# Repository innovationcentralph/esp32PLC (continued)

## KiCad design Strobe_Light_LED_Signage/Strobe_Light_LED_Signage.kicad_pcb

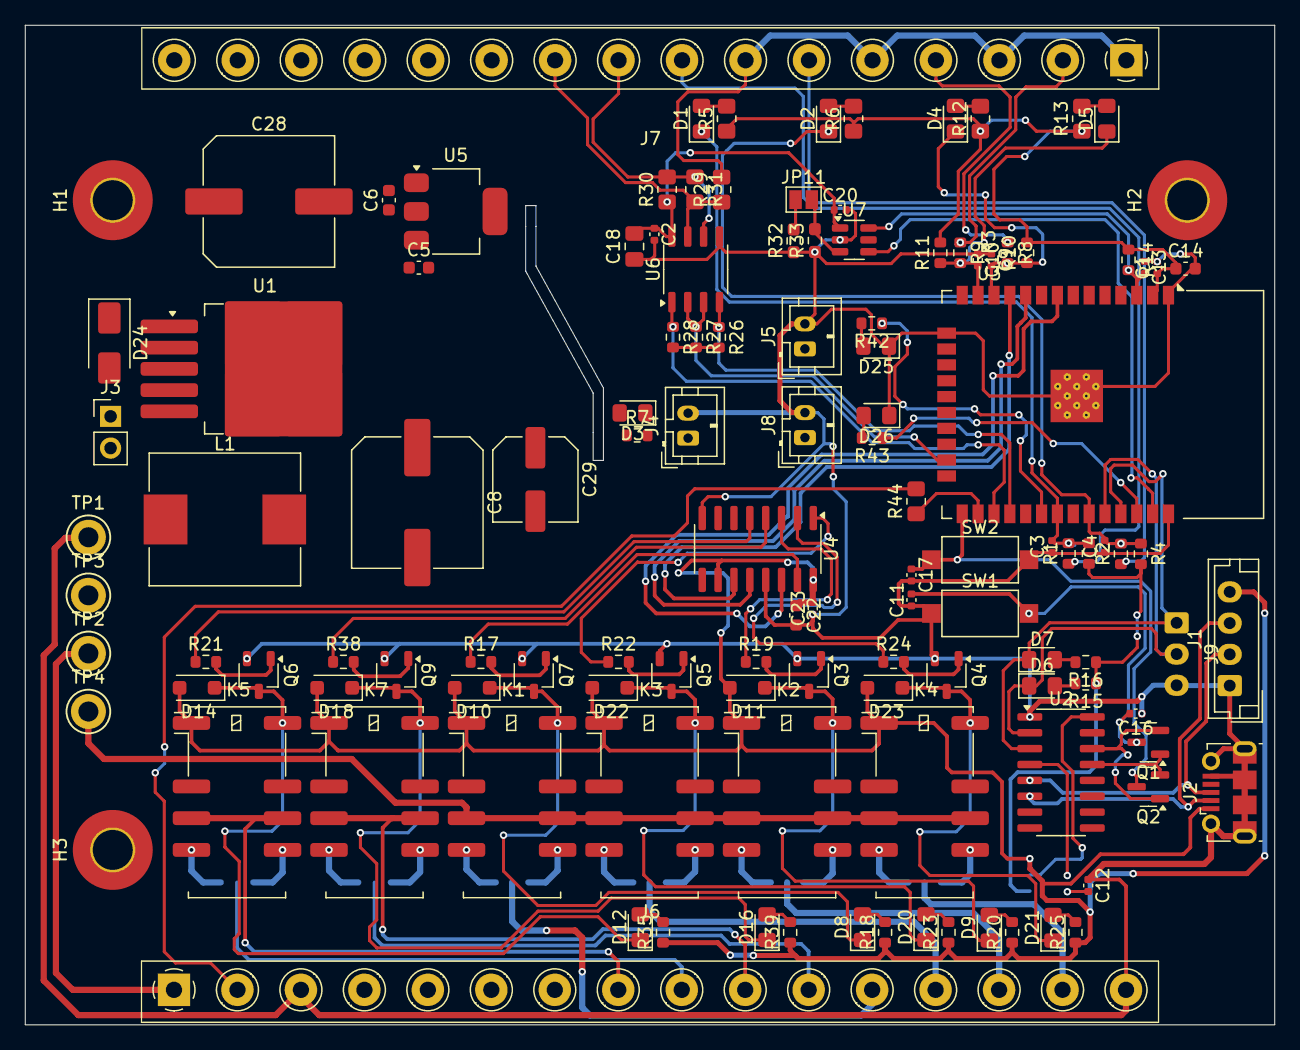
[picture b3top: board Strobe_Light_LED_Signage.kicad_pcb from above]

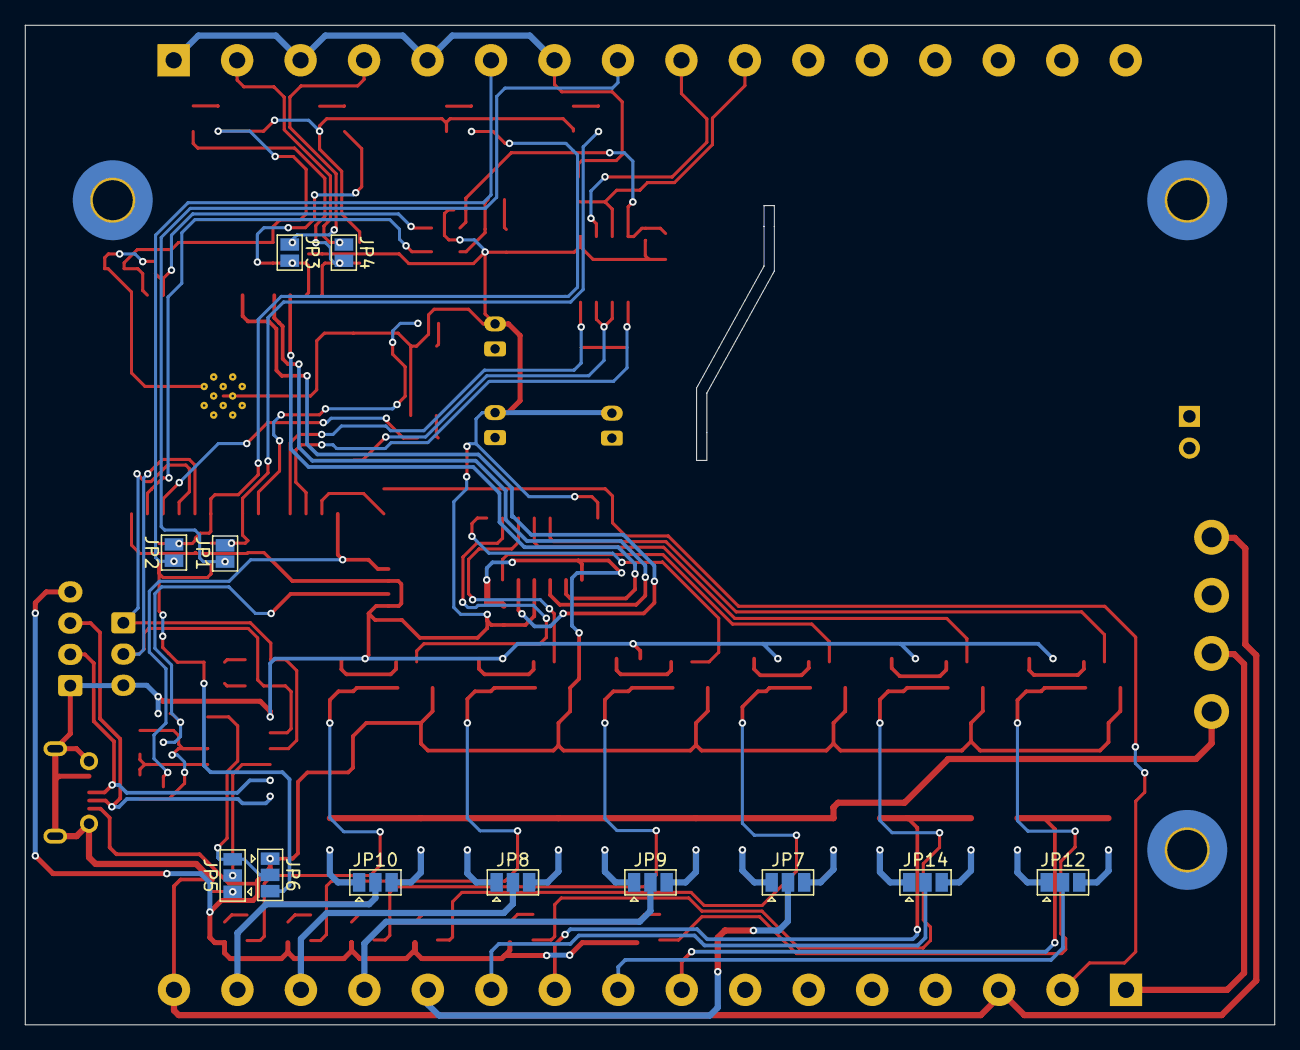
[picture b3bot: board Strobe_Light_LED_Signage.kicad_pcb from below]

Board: 2 copper layers, 100.0 x 80.0 mm, 135 parts (12 on the bottom side), 93 nets.

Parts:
C1, C2, C3, C4, C9, C10, C11, C12, C13, C16, C17, C20, C23: 0.1uF; C_0402_1005Metric
C5, C6, C14, C22: 22uF; C_0603_1608Metric
C8: 1000uF; C_Elec_10x10.2
C18: 10uF; C_0805_2012Metric_Pad1.18x1.45mm_HandSolder
C28: 100uF; C_Elec_10x10.2
C29: 220uF; C_Elec_6.3x7.7
D1, D2, D3, D4, D5, D6, D7, D8, D9, D12, D16, D20, D21, D25, D26: LED; LED_0805_2012Metric_Pad1.15x1.40mm_HandSolder
D10, D11, D14, D18, D22, D23: DIODE; D_SOD-123F
D24: SS54; D_SMA
H1, H2, H3: MountingHole; MountingHole_3.2mm_M3_Pad_TopBottom
J1: Conn_01x04_Socket; JST_EH_B4B-EH-A_1x04_P2.50mm_Vertical
J2: USB_B_Micro; USB_Micro-B_Molex-105017-0001
J3: Conn_01x02_Socket; PinHeader_1x02_P2.54mm_Vertical
J4, J5, J8: Conn_01x02_Socket; JST_PH_B2B-PH-K_1x02_P2.00mm_Vertical
J6, J7: Screw_Terminal_01x16; TerminalBlock_Phoenix_MKDS-1,5-16-5.08_1x16_P5.08mm_Horizon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
J9: Conn_01x03_Socket; JST_EH_B3B-EH-A_1x03_P2.50mm_Vertical
JP1, JP2, JP3, JP4, JP11: SolderJumper_2_Open; SolderJumper-2_P1.3mm_Open_Pad1.0x1.5mm
JP5, JP6, JP7, JP8, JP9, JP10, JP12, JP14: SolderJumper_3_Open; SolderJumper-3_P1.3mm_Open_Pad1.0x1.5mm
K1, K2, K3, K4, K5, K7: EE2-5NU; Relay_DPDT_Kemet_EE2_NU
L1: 33uH; L_Chilisin_BMRF00101040
Q1, Q2: BSS138; SOT-23
Q3, Q4, Q5, Q6, Q7, Q9: Q_NPN_BEC; TSOT-23
R1, R2, R3, R4, R7, R8, R9, R10, R11, R14, R15, R16, R17, R18, R19, R20, R21, R22, R23, R24, R25, R26, R27, R28, R35, R38, R39, R42, R43: 1K; R_0603_1608Metric
R5, R6, R12, R13: 220; R_0805_2012Metric_Pad1.20x1.40mm_HandSolder
R29, R30: 20K; R_0805_2012Metric_Pad1.20x1.40mm_HandSolder
R31: 120; R_0805_2012Metric_Pad1.20x1.40mm_HandSolder
R32: 10K; R_0603_1608Metric_Pad0.98x0.95mm_HandSolder
R33: 40.2K; R_0603_1608Metric_Pad0.98x0.95mm_HandSolder
R44: 330; R_0805_2012Metric_Pad1.20x1.40mm_HandSolder
SW1, SW2: SW_Push; SW_SPST_CK_RS282G05A3
TP1, TP2, TP3, TP4: TestPoint; TestPoint_Keystone_5005-5009_Compact
U1: LM2596S-5; TO-263-5_TabPin3
U2: CH340C; SOP-16_3.9x9.9mm_P1.27mm
U3: ESP32-WROOM-32
U4: 74HC595; SOIC-16_3.9x9.9mm_P1.27mm
U5: AMS1117-3.3; SOT-223-3_TabPin2
U6: MAX485E; SOP-8_3.9x4.9mm_P1.27mm
U7: TPL5010; SOT-23-6

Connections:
5V: C2.1, C5.1, C8.1, C18.2, C20.1, C22.1, C23.2, C29.1, D10.2 (A), D11.2 (A), D14.2 (A), D18.2 (A), D22.2 (A), D23.2 (A), J1.4, J2.1 (VBUS), J3.2, J6.1, J7.14, JP6.1 (A), K1.1, K2.1, K3.1, K4.1, K5.1, K7.1, L1.2, R7.1, R18.1, R20.1, R23.1, R25.1, R26.2, R27.2, R28.2, R30.1, R35.1, R39.1, TP2.1, U4.10 (~SRCLR), U4.16 (VCC), U5.3 (VI), U6.8 (VCC), U7.1 (VDD)
24V: C28.1, J7.16, K1.4, K1.9, K2.4, K2.9, K3.4, K3.9, K4.4, K4.9, TP4.1, U1.1 (VIN)
+3.3V: C1.1, C6.1, C14.1, JP6.3 (B), R3.2, R4.2, R5.1, R6.1, R10.2, R11.2, R12.1, R13.1, R14.1, R15.1, R16.1, TP3.1, U3.2 (VDD), U5.2 (VO)
/D+: J1.2, J2.3 (D+), U2.5 (UD+)
/D-: J1.3, J2.2 (D-), U2.6 (UD-)
DC1: R21.1, U4.5 (QF)
DC1_A: J6.8, K5.4, K5.9
DC1_B: J6.9, JP12.2 (C)
DC2: R38.1, U4.4 (QE)
DC2_A: J6.10, K7.4, K7.9
DC2_B: J6.11, JP14.2 (C)
ESP_EN: C11.2, C13.2, C16.2, Q1.3 (D), R14.2, SW1.2, U3.3 (EN), U7.6 (~RST)
ESP_I0: C17.1, Q2.3 (D), SW2.1, U3.25 (IO0)
ESP_RX: D6.1 (K), J9.2, U2.2 (TXD), U3.34 (RXD0/IO3)
ESP_TX: D7.1 (K), J9.1, U2.3 (RXD), U3.35 (TXD0/IO1)
GND: C1.2, C2.2, C3.1, C4.1, C5.2, C6.2, C8.2, C9.1, C10.1, C11.1, C12.1, C13.1, C14.2, C16.1, C17.2, C18.1, C20.2, C22.2, C23.1, C28.2, C29.2, D3.1 (K), D24.2 (A), D25.1 (K), D26.1 (K), J1.1, J2.5 (GND), J2.6 (Shield), J4.2, J5.2, J6.3, J6.16, J7.1, J7.3, J7.5, J7.7, J7.13, J7.15, J8.2, J9.3, Q3.2 (E), Q4.2 (E), Q5.2 (E), Q6.2 (E), Q7.2 (E), Q9.2 (E), R29.2, R32.1, R33.1, SW1.1, SW2.2, TP1.1, U1.3 (GND), U1.5 (~ON/OFF), U2.1 (GND), U3.1 (GND), U3.15 (GND), U3.38 (GND), U3.39 (GND), U4.8 (GND), U4.13 (~OE), U5.1 (GND), U6.5 (GND), U7.2 (GND)
IN1: C3.2, D1.1 (K), JP1.2 (B), R1.2, R3.1, U3.31 (IO19)
IN1_A: J7.8, JP1.1 (A), R1.1
IN2: C4.2, D2.1 (K), JP2.2 (B), R2.2, R4.1, U3.33 (IO21)
IN2_A: J7.6, JP2.1 (A), R2.1
IN3: C9.2, D4.1 (K), JP3.2 (B), R8.2, R10.1, U3.12 (IO27)
IN3_A: J7.4, JP3.1 (A), R8.1
IN4: C10.2, D5.1 (K), JP4.2 (B), R9.2, R11.1, U3.13 (IO14)
IN4_A: J7.2, JP4.1 (A), R9.1
MODBUS_A: J7.10, R29.1, R31.2, U6.7 (B)
MODBUS_B: J7.9, R30.2, R31.1, U6.6 (A)
unnamed: D1.2 (A), R5.2
unnamed: D2.2 (A), R6.2
unnamed: D3.2 (A), J4.1, R7.2
unnamed: D4.2 (A), R12.2
unnamed: D5.2 (A), R13.2
unnamed: D6.2 (A), R15.2
unnamed: D7.2 (A), R16.2
unnamed: D8.2 (A), R18.2
unnamed: D9.2 (A), R20.2
unnamed: D8.1 (K), D10.1 (K), K1.12, Q7.3 (C)
unnamed: D9.1 (K), D11.1 (K), K2.12, Q3.3 (C)
unnamed: D12.2 (A), R35.2
unnamed: D12.1 (K), D14.1 (K), K5.12, Q6.3 (C)
unnamed: D16.2 (A), R39.2
unnamed: D16.1 (K), D18.1 (K), K7.12, Q9.3 (C)
unnamed: D20.2 (A), R23.2
unnamed: D20.1 (K), D22.1 (K), K3.12, Q5.3 (C)
unnamed: D21.2 (A), R25.2
unnamed: D21.1 (K), D23.1 (K), K4.12, Q4.3 (C)
unnamed: D24.1 (K), L1.1, U1.2 (OUT)
unnamed: D25.2 (A), J5.1, R42.2
unnamed: D26.2 (A), J8.1, R43.2
unnamed: J3.1, U1.4 (FB)
unnamed: C12.2, JP5.1 (A)
unnamed: JP5.3 (B), JP6.2 (C), U2.16 (VCC)
unnamed: JP5.2 (C), U2.4 (V3)
unnamed: JP7.1 (A), K1.8
unnamed: JP7.3 (B), K1.5
unnamed: JP8.1 (A), K2.8
unnamed: JP8.3 (B), K2.5
unnamed: JP9.1 (A), K3.8
unnamed: JP9.3 (B), K3.5
unnamed: JP10.1 (A), K4.8
unnamed: JP10.3 (B), K4.5
unnamed: JP11.1 (A), R32.2
unnamed: JP11.2 (B), R33.2, U7.3 (DELAY/M_RST)
unnamed: JP12.1 (A), K5.8
unnamed: JP12.3 (B), K5.5
unnamed: JP14.1 (A), K7.8
unnamed: JP14.3 (B), K7.5
unnamed: Q1.1 (G), Q2.2 (S), U2.13 (~DTR)
unnamed: Q1.2 (S), Q2.1 (G), U2.14 (~RTS)
unnamed: Q3.1 (B), R19.2
unnamed: Q4.1 (B), R24.2
unnamed: Q5.1 (B), R22.2
unnamed: Q6.1 (B), R21.2
unnamed: Q7.1 (B), R17.2
unnamed: Q9.1 (B), R38.2
unnamed: R44.1, U3.26 (IO4)
SLAVE_DI: R26.1, U3.28 (IO17), U6.4 (DI)
SLAVE_EN: R27.1, U3.23 (IO15), U6.2 (~RE), U6.3 (DE)
SLAVE_RO: R28.1, U3.27 (IO16), U6.1 (RO)
STATUS_CLK: U3.11 (IO26), U4.11 (SRCLK)
STATUS_CS: U3.10 (IO25), U4.12 (RCLK)
STATUS_DIN: U3.8 (IO32), U4.14 (SER)
STAT_1: R42.1, U3.30 (IO18)
STAT_2: R43.1, U3.36 (IO22)
STROBE_BUZZ: J6.15, JP10.2 (C)
STROBE_GREEN: J6.14, JP8.2 (C)
STROBE_ORANGE: J6.13, JP9.2 (C)
STROBE_RED: J6.12, JP7.2 (C)
S_BUZZ: R24.1, U4.2 (QC)
S_GREEN: R19.1, U4.3 (QD)
S_ORANGE: R22.1, U4.1 (QB)
S_RED: R17.1, U4.15 (QA)
WDT_DONE: U3.37 (IO23), U7.4 (DONE)
WS_DIN: J6.2, R44.2

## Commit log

2024-08-29 Initial Commit
    Done Strobe Light
    On Going PLC
2024-08-29 Updated PLC Arduino Project
    Added Power Isolation and Pin Mapping
2024-08-29 Added Mapping for Inputs to MUX
2024-08-30 Done Schematic ESP32 PLC
2024-08-30 Started PCB Component Placement
    To Do:
    Double Check Footprint of ADS1115
    Modularize Relay Control
    Change Big Capacitors to SMD Capacitors
2024-09-01 Done Layout PCB
    To Do Zoning
2024-09-02 Done PCB Layout PLC Board
    To DO:
    Review from Nes
    Round Corners of Strobe and PLC
    Proper Labels PLC Board
2024-09-03 Version 1.0 of both Strobe Light and PLC Done
2024-09-11 Added UPS Version 1
    Done Schematic and Component Selection from JLCPCB
2024-09-13 pcb layout
    minor schematic adjustment and pcb layout
2024-09-13 added 1x12 terminal block
    1x12 terminal block
    3d
2024-09-14 minor edits
    thermal reliefs
    front silk designations
2024-10-04 -
    edited zoning
2024-10-05 Adjusted Silk Screen Front and Back
2024-10-10 panel
2024-10-12 -
    panelization on production folder
2024-10-16 -
    updated symbol and footprint
